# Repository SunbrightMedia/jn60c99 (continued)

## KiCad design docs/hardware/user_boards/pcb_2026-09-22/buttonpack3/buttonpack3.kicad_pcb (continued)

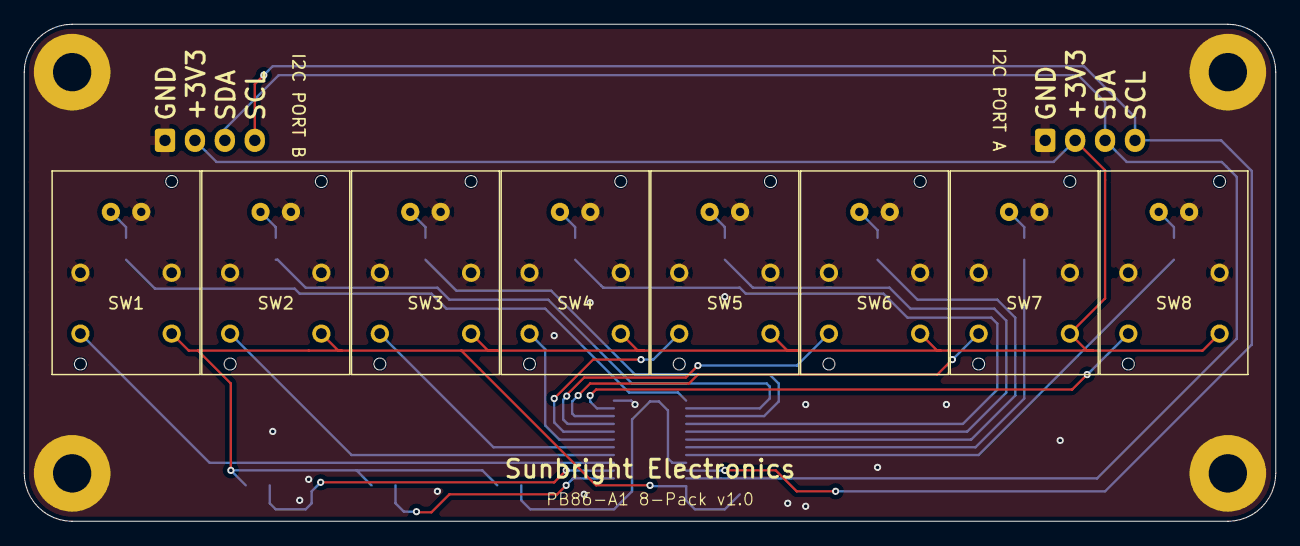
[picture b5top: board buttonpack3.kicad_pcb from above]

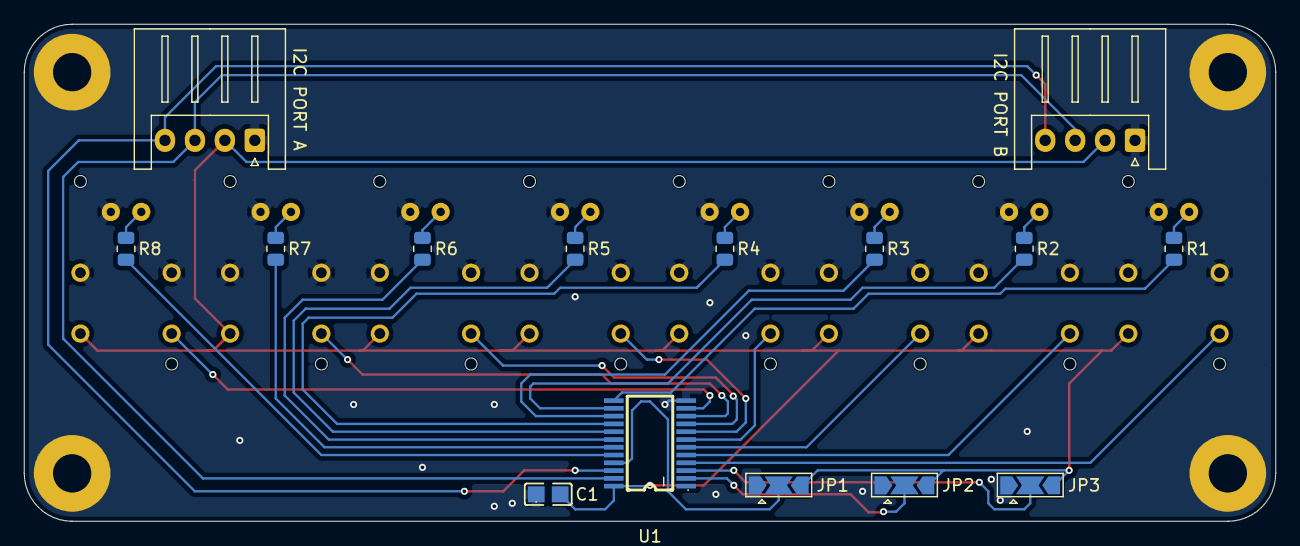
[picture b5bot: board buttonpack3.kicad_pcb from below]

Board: 2 copper layers, 104.5 x 41.5 mm, 27 parts (15 on the bottom side), 31 nets.

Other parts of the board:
I2C PORT A: I2C_IN; JST_XH_S4B-XH-A_1x04_P2.50mm_Horizontal
I2C PORT B: I2C_THRU; JST_XH_S4B-XH-A_1x04_P2.50mm_Horizontal

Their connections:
GND: I2C PORT A.1, I2C PORT B.1; also elsewhere on the board
SCL: I2C PORT A.4, I2C PORT B.4; also elsewhere on the board
SDA: I2C PORT A.3, I2C PORT B.3; also elsewhere on the board
VCC: I2C PORT A.2, I2C PORT B.2; also elsewhere on the board

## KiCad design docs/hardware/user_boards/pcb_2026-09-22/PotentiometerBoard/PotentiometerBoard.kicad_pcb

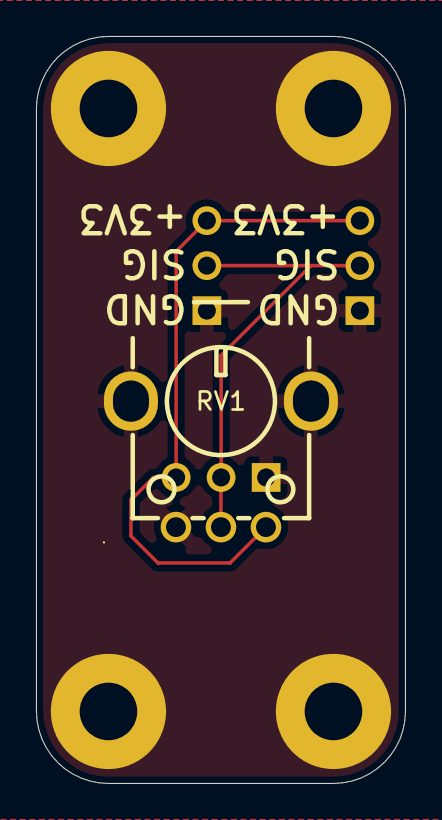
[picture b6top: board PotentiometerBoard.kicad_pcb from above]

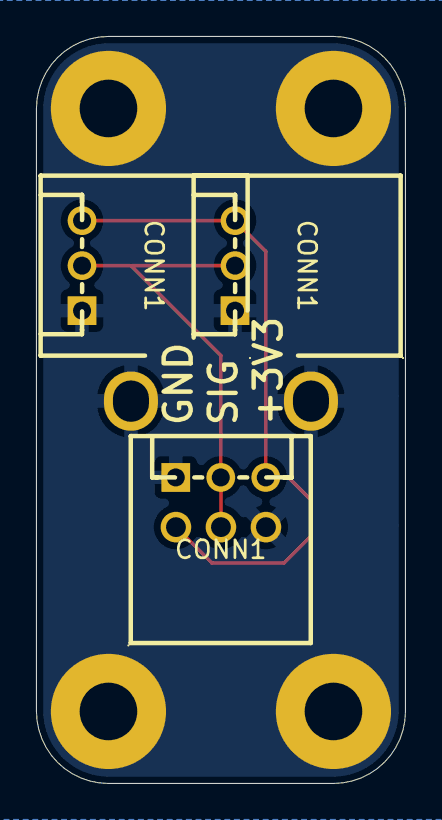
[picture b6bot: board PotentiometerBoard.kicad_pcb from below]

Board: 2 copper layers, 20.5 x 41.5 mm, 8 parts (3 on the bottom side), 3 nets.

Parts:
CONN1, CONN1#2, CONN1#3: SIGNAL; CONN-TH_S3B-XH-A-LF-SN
H1, H2, H3, H4: MountingHole_Pad; MountingHole_3.2mm_M3_Pad
RV1: RK09K1130A70; RES-TH_RK09K1130A70

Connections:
+3V3: CONN1.3, CONN1#2.3, CONN1#3.3, RV1.3
GND: CONN1.1, CONN1#2.1, CONN1#3.1, H1.1 (1_1), H2.1 (1_1), H3.1 (1_1), H4.1 (1_1), RV1.1, RV1.4 (EH), RV1.5 (EH)
SIG: CONN1.2, CONN1#2.2, CONN1#3.2, RV1.2

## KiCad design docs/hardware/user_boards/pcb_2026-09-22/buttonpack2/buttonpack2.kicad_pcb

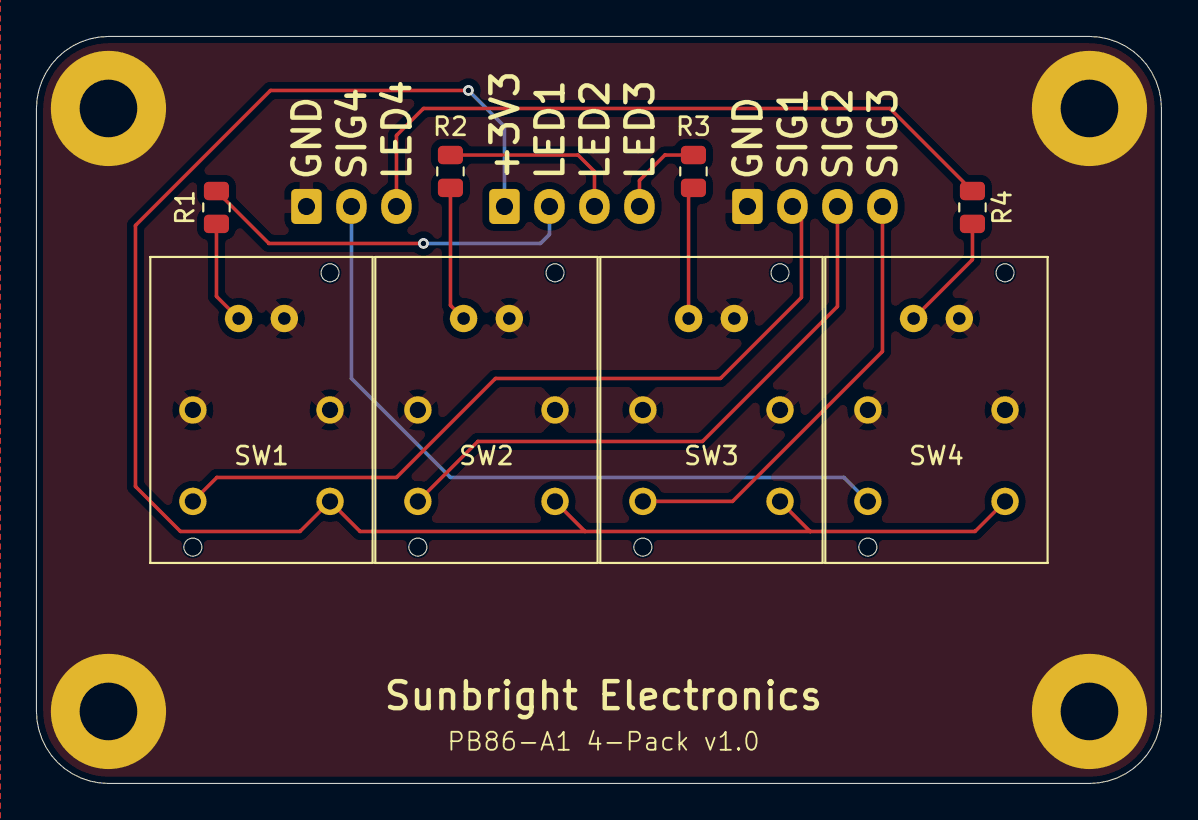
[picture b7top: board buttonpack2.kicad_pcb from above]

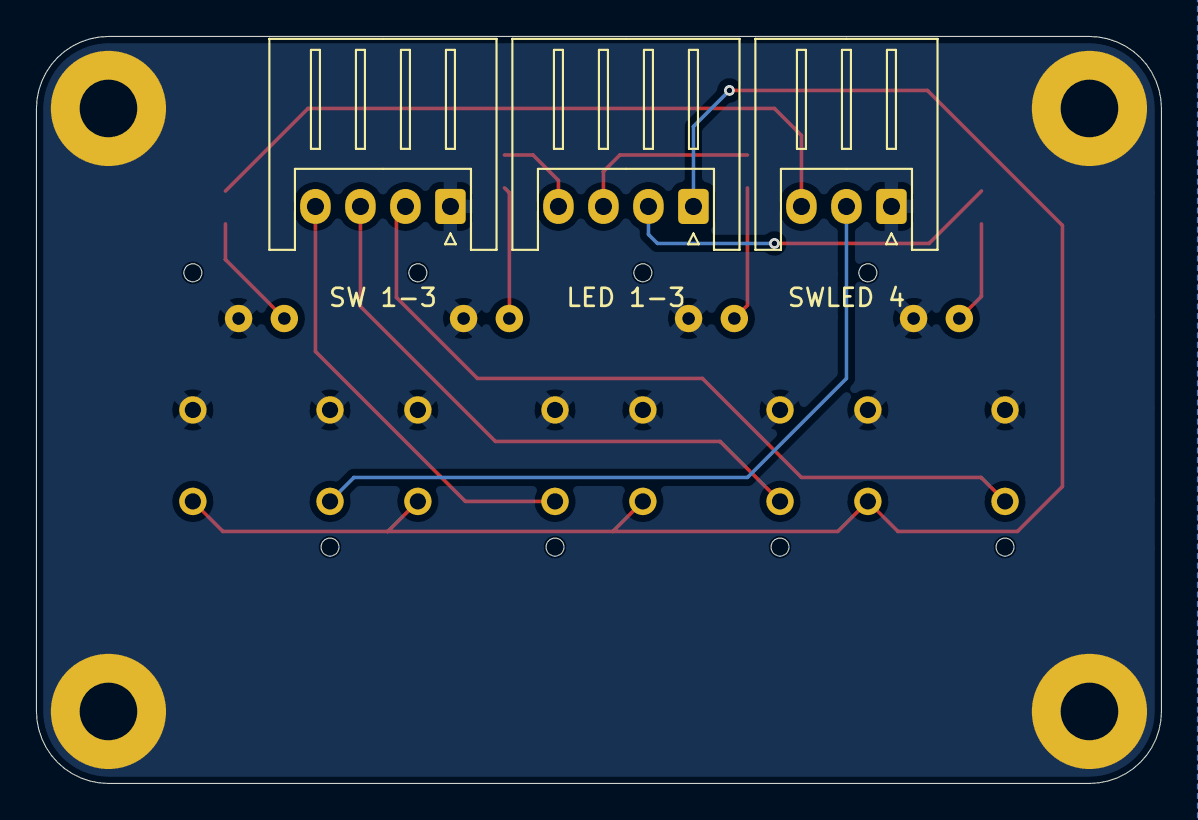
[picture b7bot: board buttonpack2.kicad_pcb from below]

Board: 2 copper layers, 62.5 x 41.5 mm, 15 parts (3 on the bottom side), 14 nets.

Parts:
H1, H2, H3, H4: HOLE_M3; MountingHole_3.2mm_M3_Pad
LED 1-3: CN_LEDs_123; JST_XH_S4B-XH-A_1x04_P2.50mm_Horizontal
R1, R2, R3, R4: 220; R_0805_2012Metric
SW1: PB86_1; PB_86_A1
SW2: PB86_2; PB_86_A1
SW3: PB86_3; PB_86_A1
SW4: PB86_4; PB_86_A1
SW 1-3: CN_Buttons_123; JST_XH_S4B-XH-A_1x04_P2.50mm_Horizontal
SWLED 4: CN_ButtonLED_4; JST_XH_S3B-XH-A_1x03_P2.50mm_Horizontal

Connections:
GND: H1.1 (PAD), H2.1 (PAD), H3.1 (PAD), H4.1 (PAD), SW1.1 (B), SW1.6 (LED-), SW2.1 (B), SW2.6 (LED-), SW3.1 (B), SW3.6 (LED-), SW4.1 (B), SW4.6 (LED-), SW 1-3.1, SWLED 4.1
LED1: LED 1-3.2, R1.1
LED2: LED 1-3.3, R2.1
LED3: LED 1-3.4, R3.1
LED4: R4.1, SWLED 4.3
unnamed: R1.2, SW1.5 (LED+)
unnamed: R2.2, SW2.5 (LED+)
unnamed: R3.2, SW3.5 (LED+)
unnamed: R4.2, SW4.5 (LED+)
SIG1: SW1.2 (C), SW 1-3.2
SIG2: SW2.2 (C), SW 1-3.3
SIG3: SW3.2 (C), SW 1-3.4
SIG4: SW4.2 (C), SWLED 4.2
VCC: LED 1-3.1, SW1.3 (A), SW2.3 (A), SW3.3 (A), SW4.3 (A)

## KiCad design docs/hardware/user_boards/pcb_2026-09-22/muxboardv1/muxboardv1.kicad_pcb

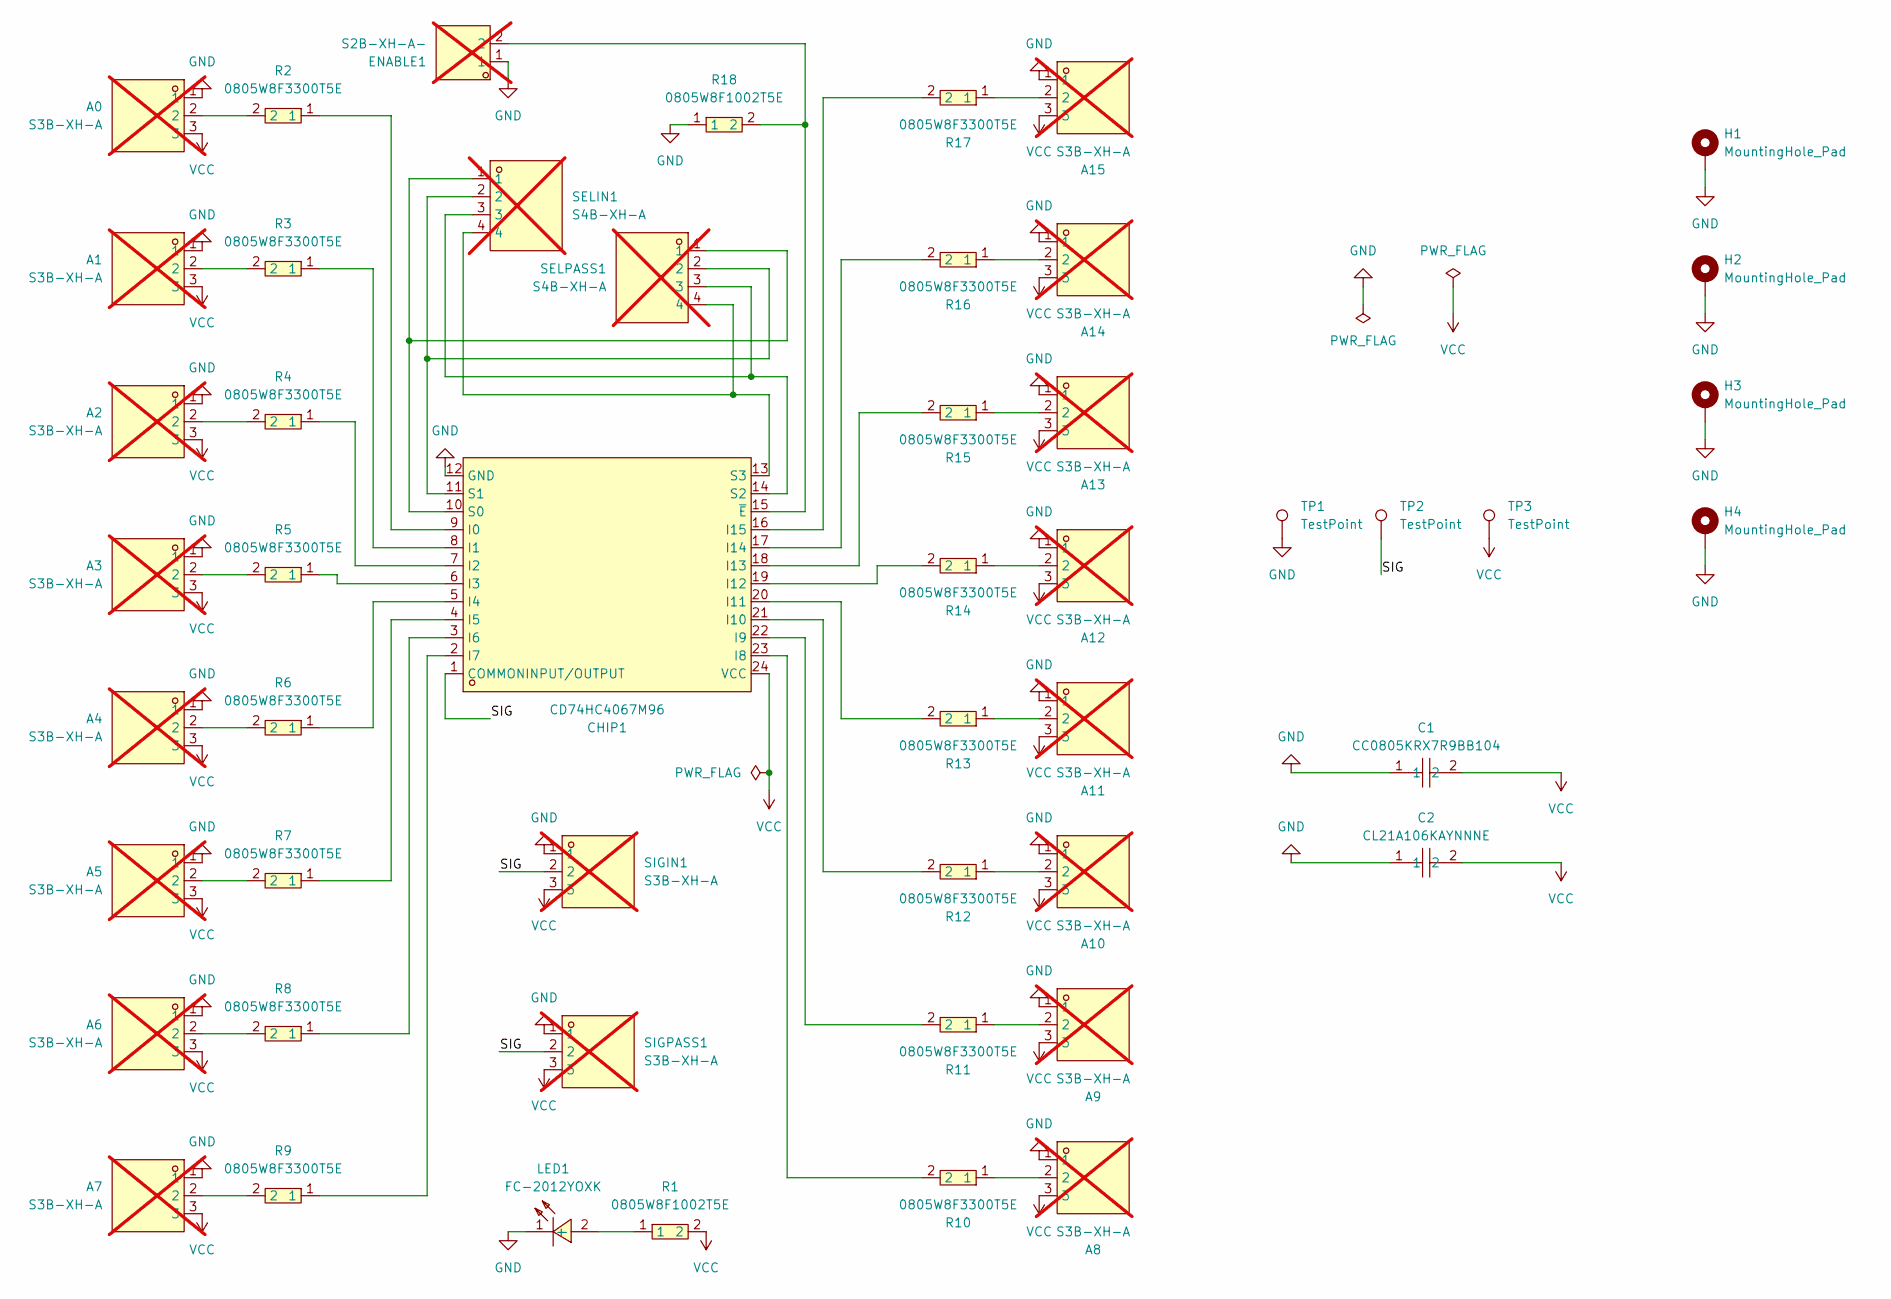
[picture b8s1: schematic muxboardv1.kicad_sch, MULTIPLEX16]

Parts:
A0, A1, A2, A3, A4, A5, A6, A7, A8, A9, A10, A11, A12, A13, A14, A15: S3B-XH-A; CONN-TH_S3B-XH-A-LF-SN; MPN S3B-XH-A(LF)(SN); LCSC Part C157928; not fitted
C1: CC0805KRX7R9BB104; C0805; MPN CC0805KRX7R9BB104; LCSC Part C49678
C2: CL21A106KAYNNNE; C0805; MPN CL21A106KAYNNNE; LCSC Part C15850
CHIP1: CD74HC4067M96; SOIC-24_L15.4-W7.5-P1.27-LS10.3-BL; MPN CD74HC4067M96; LCSC Part C496123
ENABLE1: S2B-XH-A-; CONN-TH_S2B-XH-A-LF-SN; MPN S2B-XH-A(LF)(SN); LCSC Part C157931; not fitted
H1, H2, H3, H4: MountingHole_Pad; MountingHole_3.2mm_M3_Pad
LED1: FC-2012YOXK; LED0805-RD_ORANGE; MPN NCD0805O1; LCSC Part C84262
R1, R18: 0805W8F1002T5E; R0805; MPN 0805W8F1002T5E; LCSC Part C17414
R2, R3, R4, R5, R6, R7, R8, R9, R10, R11, R12, R13, R14, R15, R16, R17: 0805W8F3300T5E; R0805; MPN 0805W8F3300T5E; LCSC Part C17630
SELIN1: S4B-XH-A; CONN-TH_S4B-XH-A-LF-SN; MPN S4B-XH-A(LF)(SN); LCSC Part C157925; not fitted
SELPASS1: S4B-XH-A; CONN-TH_S4B-XH-A-LF-SN; MPN S4B-XH-A(LF)(SN); LCSC Part C157925; not fitted
SIGIN1: S3B-XH-A; CONN-TH_S3B-XH-A-LF-SN; MPN S3B-XH-A(LF)(SN); LCSC Part C157928; not fitted
SIGPASS1: S3B-XH-A; CONN-TH_S3B-XH-A-LF-SN; MPN S3B-XH-A(LF)(SN); LCSC Part C157928; not fitted
TP1, TP2, TP3: TestPoint; TestPoint_Pad_D1.5mm

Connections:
/SIG: CHIP1.1 (COMMONINPUT/OUTPUT), SIGIN1.2, SIGPASS1.2, TP2.1
GND: A0.1, A1.1, A2.1, A3.1, A4.1, A5.1, A6.1, A7.1, A8.1, A9.1, A10.1, A11.1, A12.1, A13.1, A14.1, A15.1, C1.1, C2.1, CHIP1.12 (GND), ENABLE1.1, H1.1, H2.1, H3.1, H4.1, LED1.1 (-), R18.1, SIGIN1.1, SIGPASS1.1, TP1.1
unnamed: A0.2, R2.2
unnamed: A1.2, R3.2
unnamed: A2.2, R4.2
unnamed: A3.2, R5.2
unnamed: A4.2, R6.2
unnamed: A5.2, R7.2
unnamed: A6.2, R8.2
unnamed: A7.2, R9.2
unnamed: A8.2, R10.1
unnamed: A9.2, R11.1
unnamed: A10.2, R12.1
unnamed: A11.2, R13.1
unnamed: A12.2, R14.1
unnamed: A13.2, R15.1
unnamed: A14.2, R16.1
unnamed: A15.2, R17.1
unnamed: CHIP1.9 (I0), R2.1
unnamed: CHIP1.8 (I1), R3.1
unnamed: CHIP1.7 (I2), R4.1
unnamed: CHIP1.6 (I3), R5.1
unnamed: CHIP1.5 (I4), R6.1
unnamed: CHIP1.4 (I5), R7.1
unnamed: CHIP1.3 (I6), R8.1
unnamed: CHIP1.2 (I7), R9.1
unnamed: CHIP1.23 (I8), R10.2
unnamed: CHIP1.22 (I9), R11.2
unnamed: CHIP1.21 (I10), R12.2
unnamed: CHIP1.20 (I11), R13.2
unnamed: CHIP1.19 (I12), R14.2
unnamed: CHIP1.18 (I13), R15.2
unnamed: CHIP1.17 (I14), R16.2
unnamed: CHIP1.16 (I15), R17.2
unnamed: CHIP1.10 (S0), SELIN1.1, SELPASS1.1
unnamed: CHIP1.11 (S1), SELIN1.2, SELPASS1.2
unnamed: CHIP1.14 (S2), SELIN1.3, SELPASS1.3
unnamed: CHIP1.13 (S3), SELIN1.4, SELPASS1.4
unnamed: CHIP1.15 (~E), ENABLE1.2, R18.2
unnamed: LED1.2 (+), R1.1
VCC: A0.3, A1.3, A2.3, A3.3, A4.3, A5.3, A6.3, A7.3, A8.3, A9.3, A10.3, A11.3, A12.3, A13.3, A14.3, A15.3, C1.2, C2.2, CHIP1.24 (VCC), R1.2, SIGIN1.3, SIGPASS1.3, TP3.1

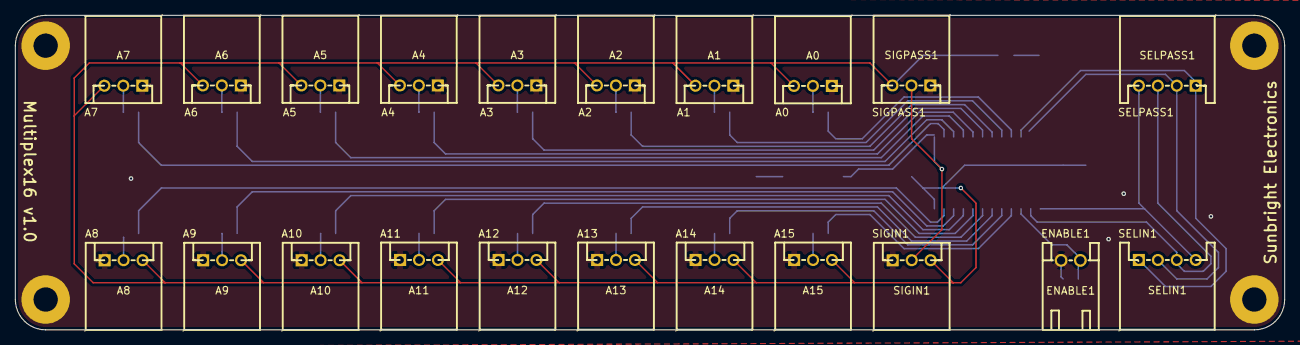
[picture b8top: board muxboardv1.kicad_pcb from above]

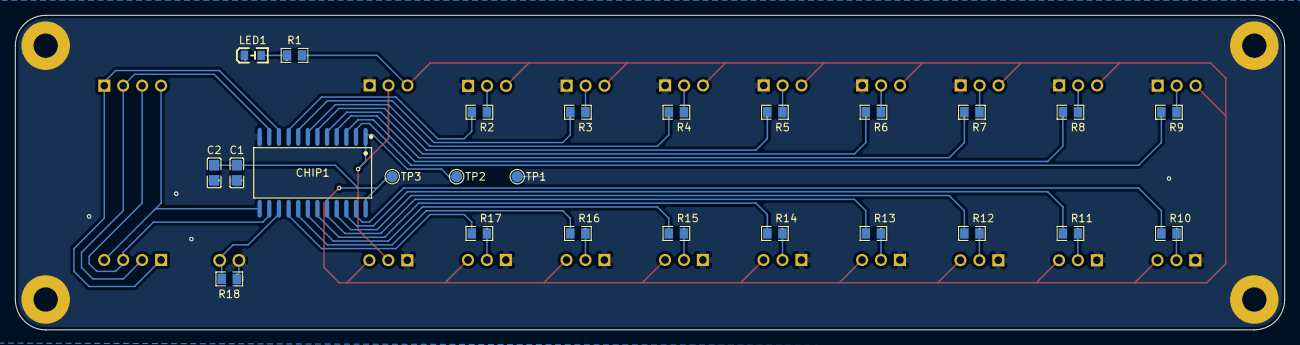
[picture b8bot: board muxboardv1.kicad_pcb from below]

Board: 2 copper layers, 167.5 x 41.5 mm, 50 parts (25 on the bottom side), 41 nets.
